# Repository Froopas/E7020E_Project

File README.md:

# Project Armory
by Josef Utbult (josutb-7@student.ltu.se) and Anton Johansson (anojoh-7@student.ltu.se)

# Specification
We plan to make a mouse wired mouse of our own design with 2 buttons(left and right), a sensor 
instead of a scroll wheel, a 7 segment display to view your progress and a RGB led strip to give 
you the gaming feeling.

## Features
- [x] Required
- [x] Display
- [ ] Custom shell
- [ ] Touch scroll 
- [ ] LED

## Parts
To make this we would need:
- A PWM3389DM-T3QU sensor ([datasheet](https://www.pixart.com/products-detail/4/PMW3389DM-T3QU))
- A [STM32F411RE](https://www.st.com/en/microcontrollers-microprocessors/stm32f411re.html#overview) MCU ([Reference Manual](https://www.st.com/resource/en/reference_manual/dm00119316-stm32f411xce-advanced-armbased-32bit-mcus-stmicroelectronics.pdf))
- A 3 digit [7 segment display](https://www.elfa.se/en/segment-led-display-mm-red-tht-everlight-electronics-elt315surwa-s530-a3/p/11068625?q=7+segment+display&pos=43&origPos=42&origPageSize=50&track=true) ([datasheet](https://www.elfa.se/Web/Downloads/_t/ds/ELT315SURWA-S530-A3_eng_tds.pdf))
- A [LED strip](https://www.elfa.se/en/ws2812b-led-strip-rgb-5v-18w-1m-seeed-studio-104990014/p/30089752?track=true&no-cache=true) ([datasheet](https://www.elfa.se/Web/Downloads/_t/ds/WS2812B_104990014_eng_tds.pdf))
- A [Resistive Linear Sensor](https://www.digikey.com/en/products/detail/spectra-symbol/SP-L-0012-103-1--RH/2175422) ([datasheet](https://media.digikey.com/pdf/Data%20Sheets/Spectra%20Symbol/SP%20Series%20SoftPot.pdf))

## Overall design

## PCB
The PCB is a standard two layer pcb, with the dimentions 40x60 mm.

## Shell
The shell is, at the moment, a 3d render from Fusion 360. It has space for the PCB in the middle 
and some plexi-glass windows to make it more visually pleasing. The buttons on the pcb are 
designed as *vertical* buttons, which means that the mecanic force from the button will have to 
come from the front of the pcb, rather than the top. This enables us to have a shell that is a 
single piece, where some cutout allows the buttons to flex and pivot around where they are joined 
to the rest of the body. The touch strip is placed under the buttons in the middle, and are mounted 
on a seperate piece that is screwed into the rest of the shell.

Shell stuff

# Result

As of 26 of March 2021 we have the following result on our project.

## Features

The hardware in place on the mouse is the mcu, the buttons, the PMW sensor and 7 segment 
display. The RGB leds that was supposed to be mounted on the pcb, and the touch sensor was left 
unmounted due to lack of time.

In software we were able to implement RTIC and got the mouse sensor, and the buttons to work with the 
HID protocol. Due to a mismatch in pin selection for the touch strip, the analog pin we chose to connect
the sensor to wasn't compatible with the HAL, which meant we could not get the ADC to work on that pin. 
Therefore, we chose to prioritize other tasks before the touch sensor. And as the RGB leds weren't in 
place we did not test these either.

The first prototype of the shell could fit the pcb and had the sensor working, but it didn't fit the 
display and was not very responsive for the buttons. A second version of this is on the way, but due to 
time constraints this will not be finished for the presentation.

## Testing

The mouse has been tested on Linux and on Windows. It worked great on Linux, but on Windows we had to 
restart the computer and pull some updates for the mouse to work. The mouse only works on very specific
surfaces, but other than that it is a functional mouse (at best).

## Evaluation

I (Josef) feel that I've could have put in more work on the software side, and less into designing the 
shell. Due to personal problems I had less time to work on it than I would have wanted. 

We feel like we've gotten an acceptable result and that the mouse is good enough for what it is.

## Future goals

We would have liked to implement the following.

* A working touch sensor that supports scrolling and scroll wheel click.

* An ergonomic shell that looks nice and is usable, with easily used mouse buttons.

* Cool led colors.

* Communication from the computer to the mouse to display killcount from CS.

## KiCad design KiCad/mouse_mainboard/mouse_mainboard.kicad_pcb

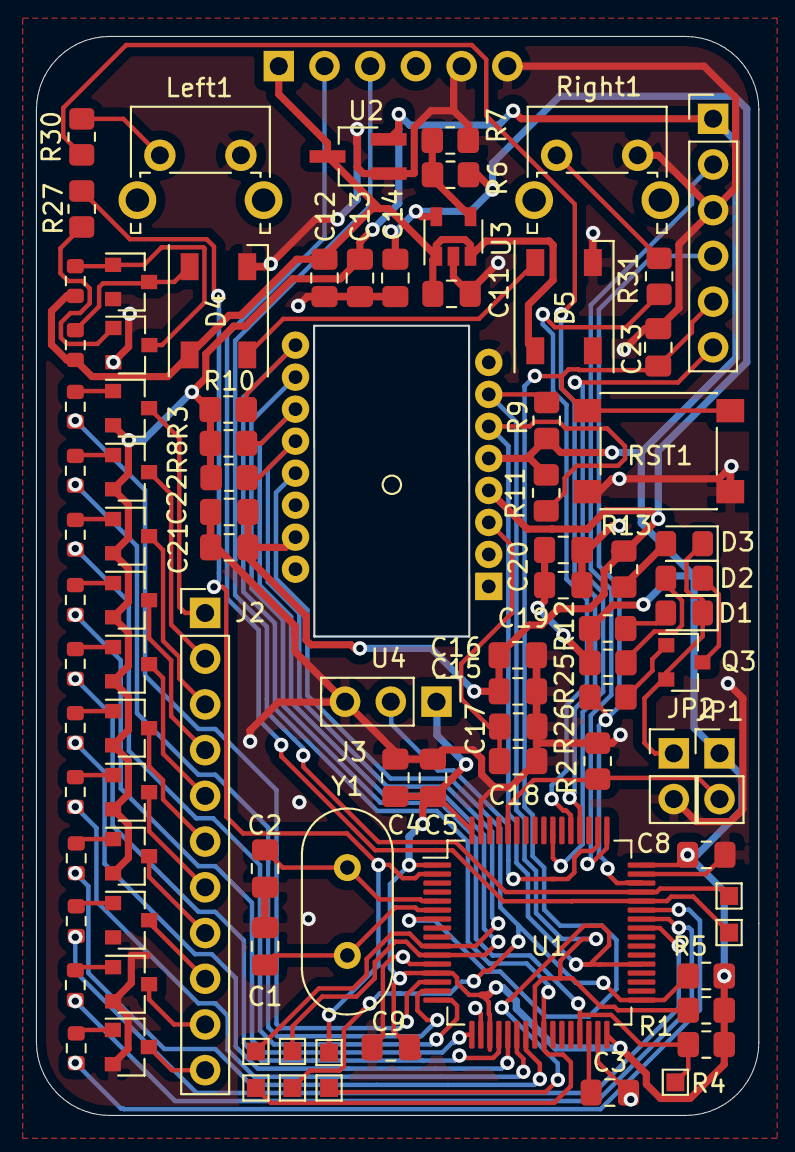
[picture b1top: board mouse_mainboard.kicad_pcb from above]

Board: 4 copper layers, 40.1 x 59.9 mm, 93 parts (1 on the bottom side), 72 nets.

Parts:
C1, C2: 47p; C_0805_2012Metric_Pad1.18x1.45mm_HandSolder
C3, C14: 2.2u; C_0805_2012Metric_Pad1.18x1.45mm_HandSolder
C4, C18: 4.7u; C_0805_2012Metric_Pad1.18x1.45mm_HandSolder
C5, C8, C9, C15, C17, C19, C21, C23: 100n; C_0805_2012Metric_Pad1.18x1.45mm_HandSolder
C11, C12, C13: 1u; C_0805_2012Metric_Pad1.18x1.45mm_HandSolder
C16, C20, C22: 10u; C_0805_2012Metric_Pad1.18x1.45mm_HandSolder
D1, D2, D3: LED; LED_0805_2012Metric_Pad1.15x1.40mm_HandSolder
D4, D5: WS2812B; LED_WS2812B_PLCC4_5.0x5.0mm_P3.2mm
J1: USB_OTG; PinHeader_1x06_P2.54mm_Vertical
J2: Conn_01x11_Male; PinHeader_1x11_P2.54mm_Vertical
J3: Conn_01x03_Male; PinHeader_1x03_P2.54mm_Vertical
JP1, JP2: Jumper; PinHeader_1x02_P2.54mm_Vertical
Left1: SW_Push; SW_Tactile_SPST_Angled_PTS645Vx58-2LFS
PrgmPrt1: Conn_01x06_Male; PinHeader_1x06_P2.54mm_Vertical
Q1, Q2, Q4, Q5, Q6, Q8, Q10, Q12: BC807; SOT-23
Q3, Q7, Q9, Q11, Q13, Q14: BC817; SOT-23
R1, R2, R3, R4, R5, R7, R8, R9, R10, R11: 10k; R_0805_2012Metric_Pad1.20x1.40mm_HandSolder
R6: 5.6K; R_0805_2012Metric_Pad1.20x1.40mm_HandSolder
R12, R25: 750R; R_0805_2012Metric_Pad1.20x1.40mm_HandSolder
R13: 50R; R_0805_2012Metric_Pad1.20x1.40mm_HandSolder
R14, R15, R16, R17, R18, R19, R20, R21, R22, R23, R24, R28, R29: 1k; R_0603_1608Metric
R26, R27, R30, R31: 1k; R_0805_2012Metric_Pad1.20x1.40mm_HandSolder
RST1: SW_Push; SW_Push_1P1T_NO_6x6mm_H9.5mm
Right1: SW_Push; SW_Tactile_SPST_Angled_PTS645Vx58-2LFS
TP1, TP2, TP3, TP4, TP5, TP6, TP7, TP8, TP9: TestPoint; TestPoint_Pad_1.0x1.0mm
U1: STM32F411RETx; LQFP-64_10x10mm_P0.5mm
U2: AP2125N-3.3TRG1; SOT-23W_Handsoldering
U3: MIC5235YM5-TR; SOT-23-5
U4: PMW3389; PWM3389DM-T3QU
Y1: Crystal; Crystal_HC49-4H_Vertical

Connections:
+5V: C11.1, C12.1, D4.1, D5.1, J1.1, R28.1, R29.1, U2.3, U3.1, U3.3
GND: C1.2, C2.1, C3.2, C4.2, C5.2, C8.1, C9.1, C11.2, C12.2, C13.2, C14.2, C15.1, C16.1, C17.1, C18.1, C19.1, C20.1, C21.1, C22.1, C23.2, D4.3, D5.3, J1.5, J1.6, J3.3, JP2.2, Left1.2, PrgmPrt1.3, Q7.2, Q9.2, Q11.2, Q13.2, Q14.2, R2.2, R7.1, RST1.2, Right1.2, U1.12, U1.18, U1.31, U1.47, U1.63, U2.1, U3.2, U4.8
unnamed: C1.1, U1.6, Y1.1
unnamed: C2.2, U1.5, Y1.2
unnamed: C3.1, U1.30
unnamed: C17.2, C18.2, U4.3
unnamed: D1.1, D3.1, JP2.1, Q3.2
unnamed: D1.2, R12.2
unnamed: D2.1, Q3.3
unnamed: D2.2, R25.2
unnamed: D3.2, R13.2
unnamed: D4.2, D5.4
unnamed: D4.4, Q14.3, R29.2
unnamed: J2.1, Q12.3
unnamed: J2.2, Q10.3
unnamed: J2.3, Q8.3
unnamed: J2.4, Q6.3
unnamed: J2.5, Q5.3
unnamed: J2.6, Q4.3
unnamed: J2.7, Q2.3
unnamed: J2.8, Q1.3
unnamed: J2.9, Q7.3
unnamed: J2.10, Q9.3
unnamed: J2.11, Q11.3
unnamed: JP1.2, R2.1, U1.60
unnamed: Left1.1, R30.1
unnamed: Q1.1, R24.1
unnamed: Q2.1, R23.1
unnamed: Q3.1, R26.2
unnamed: Q4.1, R22.1
unnamed: Q5.1, R20.1
unnamed: Q6.1, R18.1
unnamed: Q7.1, R17.2
unnamed: Q8.1, R16.1
unnamed: Q9.1, R19.2
unnamed: Q10.1, R15.1
unnamed: Q11.1, R21.2
unnamed: Q12.1, R14.1
unnamed: Q13.1, R27.2
unnamed: Q13.3, Q14.1, R28.2
unnamed: R6.1, R7.2, U3.4
unnamed: R31.1, Right1.1
VDD: C14.1, C15.2, C16.2, C21.2, C22.2, R6.2, R13.1, U3.5, U4.4, U4.15
btn_l: R30.2, U1.52
btn_r: R31.2, U1.53
disp_1: R14.2, U1.14
disp_2: R15.2, U1.15
disp_3: R16.2, U1.16
disp_4: R18.2, U1.17
disp_5: R20.2, U1.20
disp_6: R22.2, U1.21
disp_7: R23.2, U1.22
disp_8: R24.2, U1.23
disp_d1: R17.1, U1.41
disp_d2: R19.1, U1.42
disp_d3: R21.1, U1.43
led_d: R27.1, TP5.1, U1.2
mcu_cap: C4.1, C5.1, C8.2, C9.2, C13.1, C19.2, C20.2, J3.1, JP1.1, PrgmPrt1.1, Q1.2, Q2.2, Q4.2, Q5.2, Q6.2, Q8.2, Q10.2, Q12.2, R1.1, R3.1, R4.1, R5.1, R8.2, R9.2, R10.2, R11.2, R12.1, R25.1, U1.1, U1.13, U1.19, U1.32, U1.48, U1.64, U2.2, U4.5
miso: R8.1, TP2.1, U1.10, U4.12
mosi: R3.2, TP1.1, U1.11, U4.11
ncs: R5.2, TP9.1, U1.33, U4.13
pwm_gpo: R11.1, TP4.1, U1.37, U4.6
pwm_int: R10.1, TP3.1, U1.25, U4.9
pwm_rst: R1.2, R9.1, U1.24, U4.7
sclk: R4.2, TP8.1, U1.29, U4.10
strip_out: J3.2, U1.50
sw_clk: PrgmPrt1.2, U1.49
sw_io: PrgmPrt1.4, R26.1, U1.46
sw_o: PrgmPrt1.6, U1.55
sw_rst: C23.1, PrgmPrt1.5, RST1.1, U1.7
usb_d+: J1.3, TP7.1, U1.45
usb_d-: J1.2, TP6.1, U1.44

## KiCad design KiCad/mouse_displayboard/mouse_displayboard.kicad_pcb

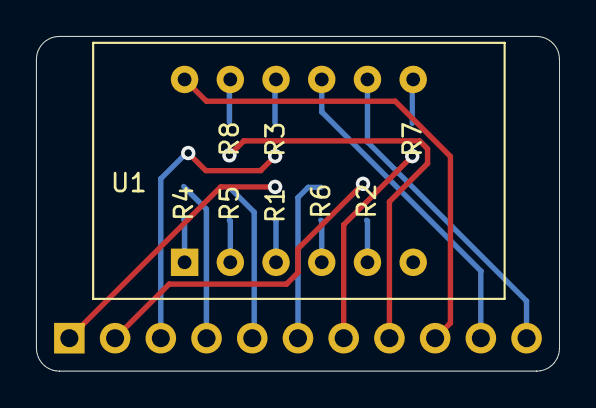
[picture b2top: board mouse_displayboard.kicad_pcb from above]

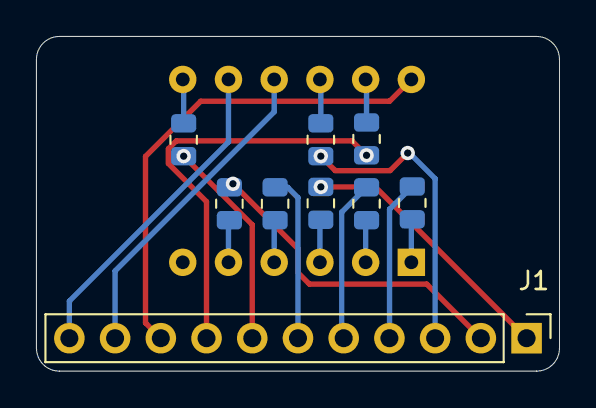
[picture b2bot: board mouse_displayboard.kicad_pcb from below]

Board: 2 copper layers, 29.1 x 18.6 mm, 10 parts (9 on the bottom side), 19 nets.

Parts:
J1: Conn_01x11_Male; PinHeader_1x11_P2.54mm_Vertical
R1, R2, R3, R4, R5, R6, R7, R8: 220R; R_0805_2012Metric
U1: 7_Segment_Display_3_char; 7 Segment Display 3 char

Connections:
unnamed: J1.1, R1.1
unnamed: J1.2, R2.1
unnamed: J1.3, R3.1
unnamed: J1.4, R4.1
unnamed: J1.5, R5.1
unnamed: J1.6, R6.1
unnamed: J1.7, R7.1
unnamed: J1.8, R8.1
unnamed: J1.9, U1.12
unnamed: J1.10, U1.9
unnamed: J1.11, U1.8
a: R8.2, U1.11
b: R7.2, U1.7
c: R6.2, U1.4
d: R5.2, U1.2
dpx: R1.2, U1.3
e: R4.2, U1.1
f: R3.2, U1.10
g: R2.2, U1.5

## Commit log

2021-01-19 Init kicad files and some notes
2021-01-19 Fixed links
2021-01-22 Added Components diagram.drawio
2021-01-22 Added initial components and created a display board
2021-01-26 Init layout and fixed wiring
2021-01-26 Added test points
2021-01-28 Added pot strip port
2021-01-29 Sorry about the image...
2021-01-29 Add images of shell render
2021-01-29 Add picture of pcb
2021-01-29 updated image of design
2021-01-29 moved design to img folder
2021-02-01 Changed display board and created a new component
2021-02-05 Add layer, fixed references and added logo
2021-02-09 Added resistors for display-board
2021-02-10 Added Changelog and TODO
2021-02-10 addes tuff in todo
2021-02-12 Connected display
2021-02-12 Fixed footprints
2021-03-16 setup of source
2021-03-16 added target to gitignore
2021-03-16 started working on pmw reading and reporting
2021-03-17 mouse does not get pulled
2021-03-18 button and sensor movement works
2021-03-23 Add scroll variables for usb poll
2021-03-26 Display working
2021-03-26 Add report
2021-03-26 Added temperature analog reading
2021-03-26 cleanup
2021-03-26 Add temperature reading
2021-03-26 display temp
2021-03-26 Add picture
2021-03-26 Add image
2021-04-09 demo v1
2021-06-01 Added comment for linear temperature function
2021-06-01 Scroll now works :)
